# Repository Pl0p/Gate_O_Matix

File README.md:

#   Gate sequencer
  *Update 09 DEC 2021*

##   64 step sequencer, 8 parts, multiple play mode, eurorack format.

###   TODO :
      
- ####     SCHEMATIC & PCB
	 - [ ] Resistor value for LED & screen
	 - [ ] Re-drawing Main_board
	 - [ ] Drawing CPU_board
	 - [ ] Drawing Output_board

- #### SOFTWARE
	 - [ ] Refont in VScode
	 - [ ] Clock multiplier/divider per part
	 - [ ] Detect clock internal/external (switching jack)
	 - [ ] Reset -> interupt
	 - [ ] Patern choice
	 - [ ] Save/Load (SD card)

 - #### HARDWARE
	 - [ ] Add SD card
	 - [ ] 12v alimentation
	 - [ ] Buffered output

##   FUNCTIONS :
#### Buttons  :
	-  Step on/off
	-  Shift + step button = step jump
	-  Fill
	-  Fill + shift = Clear
	-  Copy/Paste
	-  Copy/Paste + shift = Save
	-  Pause/Play
	-  Pause/Play + shift = Stop

#### Encoders :
	- Tempo
	- Tempo + push = clock divider
	- Gate length
	- Gate length + push = Number of step
	- Page navigation
	- Page navigation + push = Play mode
	  
#### Selecter :
	- Part choice

#### Play mode :
	- Forward
	- Backward
	- Ping Pong
	- Random
	- Brownien

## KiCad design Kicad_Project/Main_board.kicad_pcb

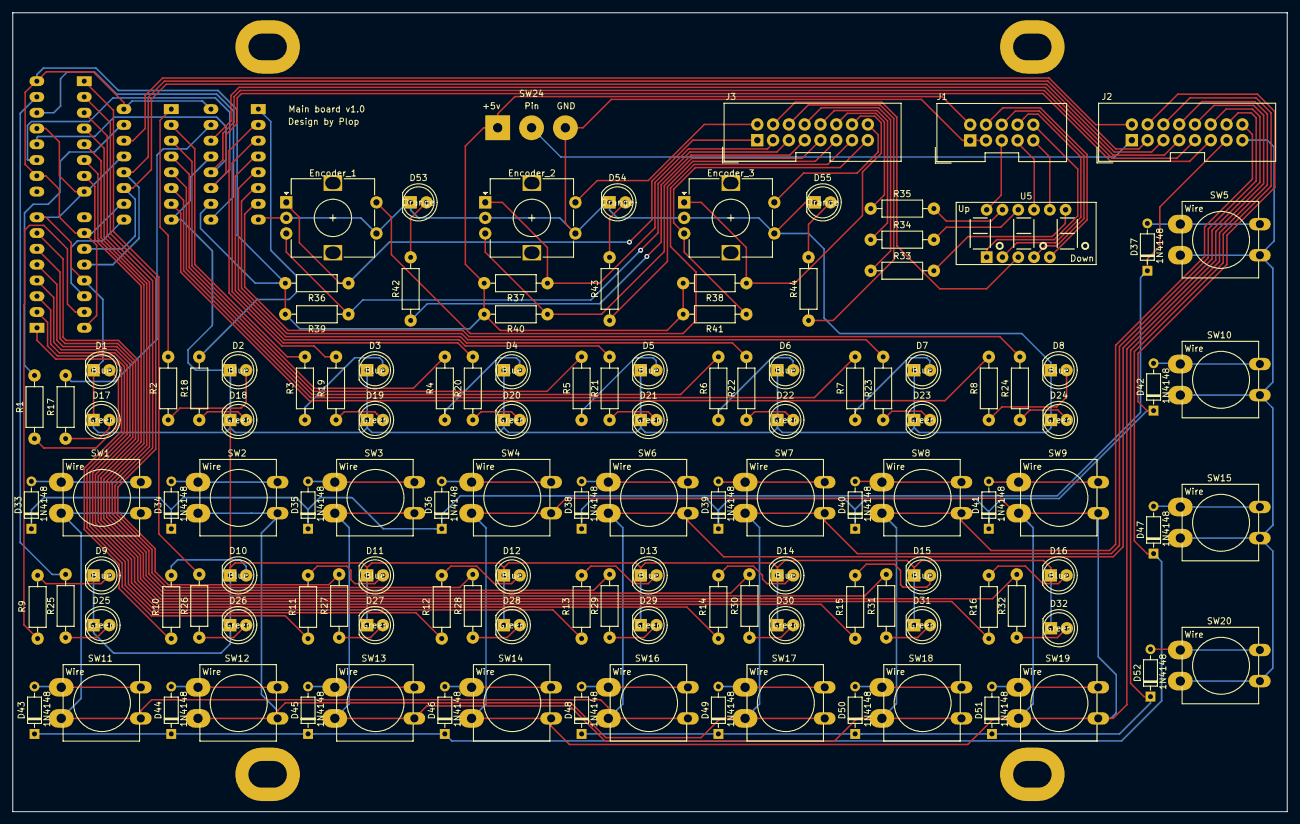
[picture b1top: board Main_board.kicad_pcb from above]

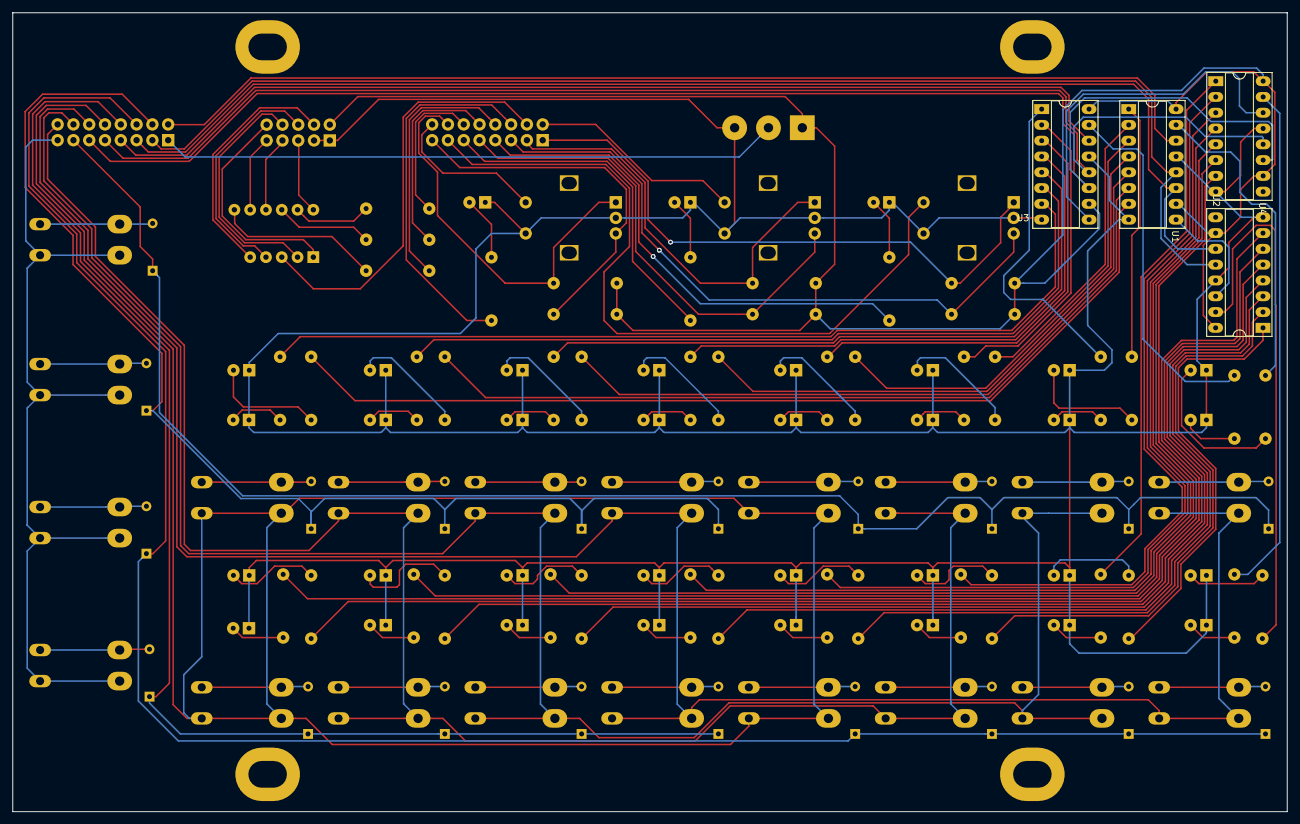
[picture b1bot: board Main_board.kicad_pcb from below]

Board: 2 copper layers, 205.0 x 128.5 mm, 131 parts (4 on the bottom side), 133 nets.

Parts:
D1, D2, D3, D4, D5, D6, D7, D8, D9, D10, D11, D12, D13, D14, D15, D16: LED_BLUE; LED_5.0mm
D17, D18, D19, D20, D21, D22, D23, D24, D25, D26, D27, D28, D29, D30, D31, D32: LED_GREEN; LED_5.0mm
D33, D34, D35, D36, D37, D38, D39, D40, D41, D42, D43, D44, D45, D46, D47, D48, D49, D50, D51, D52: 1N4148; D_DO-35_SOD27_P7.62mm_Horizontal
D53, D54, D55: LED; LED_5.0mm
Encoder_1, Encoder_2, Encoder_3: Rotary_Encoder_Switch; RotaryEncoder
J1: Data & Power; IDC-Header_2x05
J2: Data 2; IDC-Header_2x08
J3: Data 3; IDC-Header_2x08
R1, R2, R3, R4, R5, R6, R7, R8, R9, R10, R11, R12, R13, R14, R15, R16, R17, R18, R19, R20, R21, R22, R23, R24, R25, R26, R27, R28, R29, R30, R31, R32: R; Resistance
R33, R34, R35: ?; Resistance
R36, R37, R38, R39, R40, R41: 50k; Resistance
R42, R43, R44: 220; Resistance
SW1, SW2, SW3, SW4, SW5, SW6, SW7, SW8, SW9, SW10, SW11, SW12, SW13, SW14, SW15, SW16, SW17, SW18, SW19, SW20: SW_Push; SW_PUSH-12mm(deported)
SW24: Rotary_switch_8S.1P_(voltage_divider); SolderWirePad_1x03_Drill1.5mm
U1, U2, U3, U4: 74HC595; DIP-16_Socket
U5: 7_segment_3_digit_2831AS; 7-Segment_2831AS

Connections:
1: D33.1, D34.1, D35.1, D36.1, D37.1, J2.13
2: D38.1, D39.1, D40.1, D41.1, D42.1, J2.4
3: D43.1, D44.1, D45.1, D46.1, D47.1, J2.6
4: D48.1, D49.1, D50.1, D51.1, D52.1, J2.8
+5V: J1.2, R36.2, R37.2, R38.2, R39.2, R40.2, R41.2, SW24.1, U1.10, U1.16, U2.10, U2.16, U3.10, U3.16, U4.10, U4.16
A: J2.12, SW1.2, SW6.2, SW11.2, SW16.2
B: J2.14, SW2.2, SW7.2, SW12.2, SW17.2
C: J2.16, SW3.2, SW8.2, SW13.2, SW18.2
Clock_1: J2.5, U1.11, U2.11
Clock_2: J2.11, U3.11, U4.11
D: J2.10, SW4.2, SW9.2, SW14.2, SW19.2
Data_1: J2.2, U1.14
Data_2: J2.7, U3.14
E: J2.15, SW5.2, SW10.2, SW15.2, SW20.2
GND: D1.1, D2.1, D3.1, D4.1, D5.1, D6.1, D7.1, D8.1, D9.1, D10.1, D11.1, D12.1, D13.1, D14.1, D15.1, D16.1, D17.1, D18.1, D19.1, D20.1, D21.1, D22.1, D23.1, D24.1, D25.1, D26.1, D27.1, D28.1, D29.1, D30.1, D31.1, D32.1, D53.1, D54.1, D55.1, Encoder_1.C, Encoder_1.S2, Encoder_2.C, Encoder_2.S2, Encoder_3.C, Encoder_3.S2, J1.1, J1.3, SW24.3, U1.8, U1.13, U2.8, U2.13, U3.8, U3.13, U4.8, U4.13
Latch_1: J2.3, U1.12, U2.12
Latch_2: J2.9, U3.12, U4.12
unnamed: D1.2, R1.1
unnamed: D2.2, R2.1
unnamed: D3.2, R3.1
unnamed: D4.2, R4.1
unnamed: D5.2, R5.1
unnamed: D6.2, R6.1
unnamed: D7.2, R7.1
unnamed: D8.2, R8.1
unnamed: D9.2, R9.1
unnamed: D10.2, R10.1
unnamed: D11.2, R11.1
unnamed: D12.2, R12.1
unnamed: D13.2, R13.1
unnamed: D14.2, R14.1
unnamed: D15.2, R15.1
unnamed: D16.2, R16.1
unnamed: D17.2, R17.1
unnamed: D18.2, R18.1
unnamed: D19.2, R19.1
unnamed: D20.2, R20.1
unnamed: D21.2, R21.1
unnamed: D22.2, R22.1
unnamed: D23.2, R23.1
unnamed: D24.2, R24.1
unnamed: D25.2, R25.1
unnamed: D26.2, R26.1
unnamed: D27.2, R27.1
unnamed: D28.2, R28.1
unnamed: D29.2, R29.1
unnamed: D30.2, R30.1
unnamed: D31.2, R31.1
unnamed: D32.2, R32.1
unnamed: D33.2, SW1.1
unnamed: D34.2, SW2.1
unnamed: D35.2, SW3.1
unnamed: D36.2, SW4.1
unnamed: D37.2, SW5.1
unnamed: D38.2, SW6.1
unnamed: D39.2, SW7.1
unnamed: D40.2, SW8.1
unnamed: D41.2, SW9.1
unnamed: D42.2, SW10.1
unnamed: D43.2, SW11.1
unnamed: D44.2, SW12.1
unnamed: D45.2, SW13.1
unnamed: D46.2, SW14.1
unnamed: D47.2, SW15.1
unnamed: D48.2, SW16.1
unnamed: D49.2, SW17.1
unnamed: D50.2, SW18.1
unnamed: D51.2, SW19.1
unnamed: D52.2, SW20.1
unnamed: D53.2, R42.2
unnamed: D54.2, R43.2
unnamed: D55.2, R44.2
unnamed: R1.2, U1.15
unnamed: R2.2, U1.1
unnamed: R3.2, U1.2
unnamed: R4.2, U1.3
unnamed: R5.2, U1.4
unnamed: R6.2, U1.5
unnamed: R7.2, U1.6
unnamed: R8.2, U1.7
unnamed: R9.2, U2.15
unnamed: R10.2, U2.1
unnamed: R11.2, U2.2
unnamed: R12.2, U2.3
unnamed: R13.2, U2.4
unnamed: R14.2, U2.5
unnamed: R15.2, U2.6
unnamed: R16.2, U2.7
unnamed: R17.2, U3.15
unnamed: R18.2, U3.1
unnamed: R19.2, U3.2
unnamed: R20.2, U3.3
unnamed: R21.2, U3.4
unnamed: R22.2, U3.5
unnamed: R23.2, U3.6
unnamed: R24.2, U3.7
unnamed: R25.2, U4.15
unnamed: R26.2, U4.1
unnamed: R27.2, U4.2
unnamed: R28.2, U4.3
unnamed: R29.2, U4.4
unnamed: R30.2, U4.5
unnamed: R31.2, U4.6
unnamed: R32.2, U4.7
unnamed: R33.2, U5.7
unnamed: R34.2, U5.10
unnamed: R35.2, U5.11
unnamed: U1.9, U2.14
unnamed: U3.9, U4.14
Screen_A: J1.9, U5.8
Screen_B: J1.5, U5.12
Screen_C: J1.6, U5.4
Screen_CA1: J3.8, R33.1
Screen_CA2: J3.10, R34.1
Screen_CA3: J3.12, R35.1
Screen_D: J1.8, U5.2
Screen_DP: J3.4, U5.3
Screen_E: J1.10, U5.1
Screen_F: J1.7, U5.9
Screen_G: J1.4, U5.5
Selector_pin: J2.1, SW24.2
ecdr_clock_1: Encoder_1.A, J3.1, R36.1
ecdr_clock_2: Encoder_2.A, J3.3, R37.1
ecdr_clock_3: Encoder_3.A, J3.14, R38.1
ecdr_data_1: Encoder_1.B, J3.5, R39.1
ecdr_data_2: Encoder_2.B, J3.9, R40.1
ecdr_data_3: Encoder_3.B, J3.15, R41.1
ecdr_led_1: J3.7, R42.1
ecdr_led_2: J3.11, R43.1
ecdr_led_3: J3.6, R44.1
ecdr_sw_1: Encoder_1.S1, J3.13
ecdr_sw_2: Encoder_2.S1, J3.2
ecdr_sw_3: Encoder_3.S1, J3.16

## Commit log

2021-02-21 Work in progress
2021-04-11 adding gerbers
2021-04-29 Update Readme
    A better Readme thank's to RomRom <3
2021-04-29 Update Readme
    Better Readme Thank's to RomRom
2021-12-09 Refont of the projects
    VScode is used instead of Arduino IDE
    Refont of the Kicad projects (i use subsheets) it's less messy i hope
2021-12-09 new branch
